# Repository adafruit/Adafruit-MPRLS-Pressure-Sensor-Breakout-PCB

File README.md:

## Adafruit MPRLS Ported Pressure Sensor Breakout - 0 to 25 PSI PCB

<a href="http://www.adafruit.com/products/3965"><br/>
Click here to purchase one from the Adafruit shop</a>

PCB files for the Adafruit MPRLS Ported Pressure Sensor Breakout - 0 to 25 PSI. Format is EagleCAD schematic and board layout
* https://www.adafruit.com/product/3965

### Description

We stock a few barometric pressure sensors, great for altitude and weather measurements. This pressure sensor is special because it comes with a metal port! Unlike other pressure sensors, you can easily attach a tube to it, to measure air pressure inside a close space. In particular we think this would be a great sensor for use with making DIY assistive tech "Sip & Puff" interfaces, or measuring the pressure within a vacuum chamber or other pressurized container.

Unlike most ported pressure sensors, this one uses I2C, it's really easy to use with any microcontroller. Inside is a silicone-gel covered pressure sensing gauge with a pre-calibrated and compensated 24 bit ADC. We have [example code and libraries for Arduino](https://github.com/adafruit/Adafruit_MPRLS) or [CircuitPython/Python](https://github.com/adafruit/Adafruit_CircuitPython_MPRLS). You can measure absolute pressure 0 to 25 PSI, which is a great range since ambient pressure here on Earth is about 14.5 PSI.

The port is made of stainless steel and is 3.7mm long and 2.5mm diameter. It doesn't come with tubing so be sure to purchase some tubing to attach to the port.

We've placed this nice sensor on a breakout board with 3.3V power regulation and level shifting so you can use it with any kind of microcontroller or microcomputer, from an Arduino compatible to Raspberry Pi

### License

Adafruit invests time and resources providing this open source design, please support Adafruit and open-source hardware by purchasing products from [Adafruit](https://www.adafruit.com)!

Designed by Limor Fried/Ladyada for Adafruit Industries.

Creative Commons Attribution/Share-Alike, all text above must be included in any redistribution. See license.txt for additional details.

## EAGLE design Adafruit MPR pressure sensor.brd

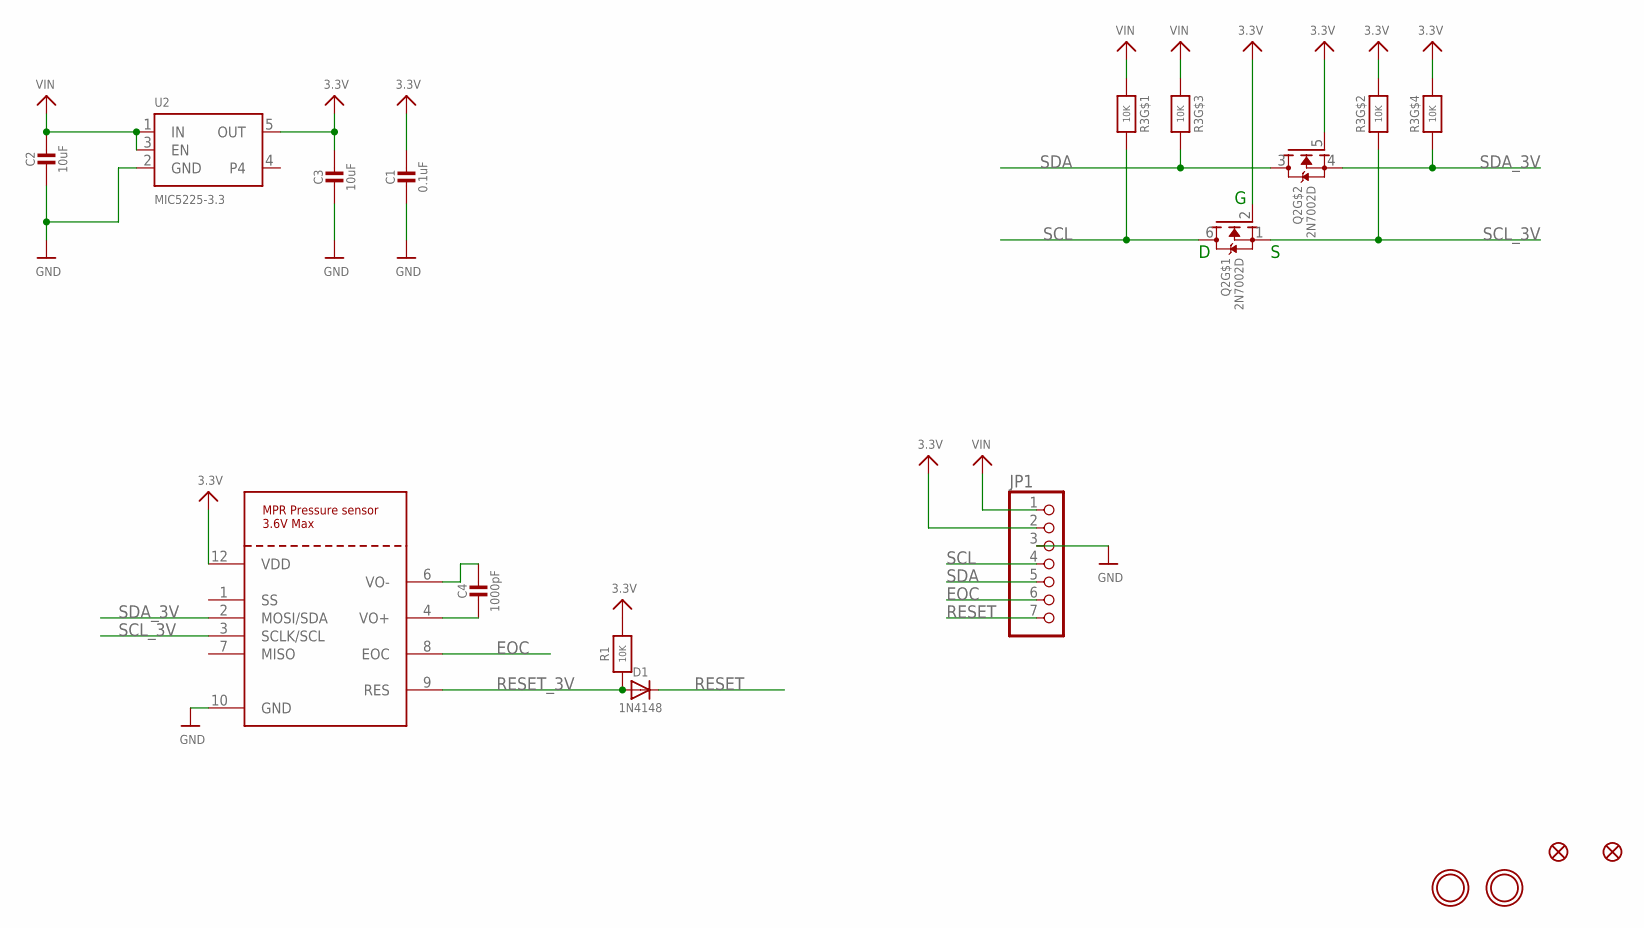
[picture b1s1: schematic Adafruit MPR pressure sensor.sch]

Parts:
C1: 0.1uF; 0603-NO
C2, C3: 10uF; 0805-NO
C4: 1000pF; 0603-NO
D1: 1N4148; SOD-323
FID1, FID2: FIDUCIAL_1MM
JP1: HEADER-1X770MIL; 1X07_ROUND_70
Q2: 2N7002D; SOT363
R1: 10K; 0603-NO
R3: 10K; RESPACK_4X0603
U2: MIC5225-3.3; SOT23-5
U$3, U$4: MOUNTINGHOLE2.5; MOUNTINGHOLE_2.5_PLATED
U$18: MPR_SERIES_I2C_PRESSURE

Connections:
3.3V: C1.1, C3.1, JP1.2, Q2.2 (G), Q2.5 (G), R1.2, R3.2 (1), R3.4 (1), U2.5 (OUT), U$18.12 (VDD)
EOC: JP1.6, U$18.8 (EOC)
GND: C1.2, C2.2, C3.2, JP1.3, U2.2 (GND), U$18.10 (GND)
unnamed: C4.2, U$18.4 (VO+)
unnamed: C4.1, U$18.6 (VO-)
RESET: D1.C, JP1.7
RESET_3V: D1.A, R1.1, U$18.9 (RES)
SCL: JP1.4, Q2.6 (D), R3.8 (2)
SCL_3V: Q2.1 (S), R3.7 (2), U$18.3 (SCLK/SCL)
SDA: JP1.5, Q2.3 (D), R3.6 (2)
SDA_3V: Q2.4 (S), R3.5 (2), U$18.2 (MOSI/SDA)
VIN: C2.1, JP1.1, R3.1, R3.3 (1), U2.1 (IN), U2.3 (EN)

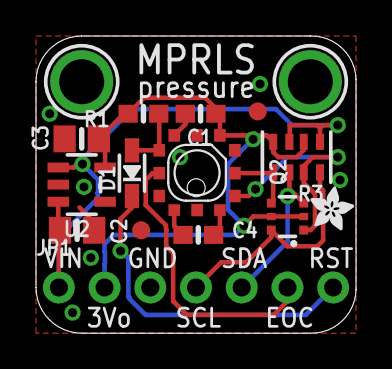
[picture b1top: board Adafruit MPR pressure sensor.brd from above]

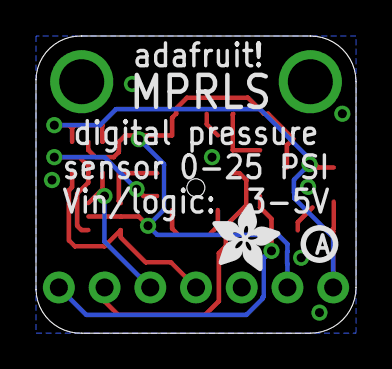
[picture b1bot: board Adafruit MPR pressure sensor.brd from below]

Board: 2 copper layers, 17.8 x 16.5 mm, 18 parts (2 on the bottom side), 12 nets.

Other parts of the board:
U$1: ADAFRUIT_3.5MM
U$8: ADAFRUIT_2.5MM
U$27: PCBFEAT-REV-040

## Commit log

2018-09-26 init
2019-07-16 updating to use the new cookiecutter for pcb repos

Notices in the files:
parts and their libraries:
microbuilder: This work is placed in the public domain, and may be freely used for commercial and non-commercial work with the following conditions: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
